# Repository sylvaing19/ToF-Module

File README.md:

# ToF-Module
Time of Flight Module for ranging measurement (hardware + software)

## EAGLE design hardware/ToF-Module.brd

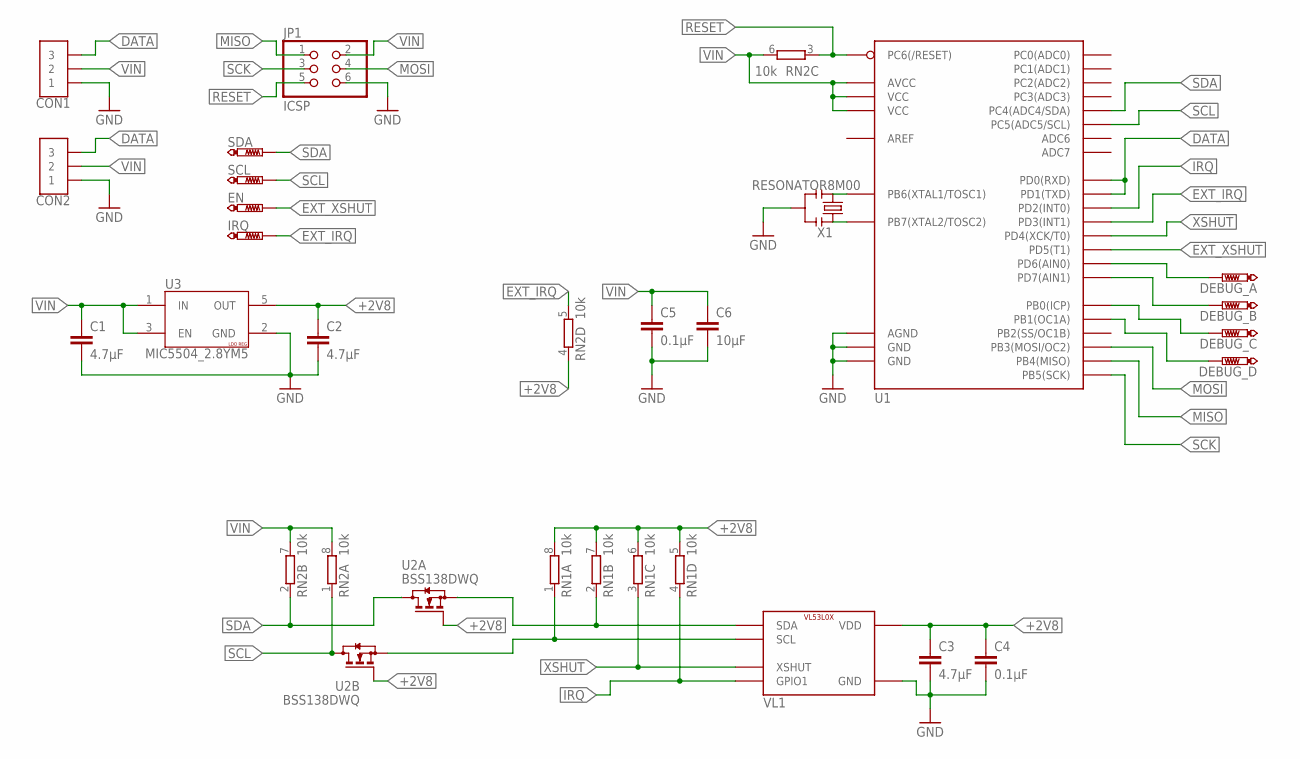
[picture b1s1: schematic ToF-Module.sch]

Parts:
C1, C2, C3: 4.7µF; C0603
C4, C5: 0.1µF; C0603
C6: 10µF; C0805
CON1, CON2: JST-03; GH-03-V
DEBUG_A: PTR1TP15R; TP15R
DEBUG_B: PTR1TP15R; TP15R
DEBUG_C: PTR1TP15R; TP15R
DEBUG_D: PTR1TP15R; TP15R
EN: PTR1TP20SQ; TP20SQ
IRQ: PTR1TP20SQ; TP20SQ
JP1: ICSP; 2X03
RN1, RN2: 10k; CAT16; MOUSER 652-CAT16-103J4LF
SCL: PTR1TP20SQ; TP20SQ
SDA: PTR1TP20SQ; TP20SQ
U1: ATMEGA328P; QFP80P900X900X120-32
U2: BSS138DWQ; SOT65P210X110-6
U3: MIC5504_2.8YM5; SOT95P280X145-5
VL1: VL53L0X
X1: RESONATOR8M00; CSTNE

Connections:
+2V8: C2.1, C3.1, C4.1, RN1.5 (2), RN1.6 (2), RN1.7 (2), RN1.8 (2), RN2.4 (1), U2.G1 (G), U2.G2 (G), U3.5 (OUT), VL1.1 (VDD), VL1.11 (VDD)
DATA: CON1.3, CON2.3, U1.30 (PD0(RXD)), U1.31 (PD1(TXD))
EXT_IRQ: IRQ.TP, RN2.5 (2), U1.1 (PD3(INT1))
EXT_XSHUT: EN.TP, U1.9 (PD5(T1))
GND: C1.2, C2.2, C3.2, C4.2, C5.2, C6.2, CON1.1, CON2.1, JP1.6, U1.3 (GND), U1.5 (AGND), U1.21 (GND), U3.2 (GND), VL1.2 (GND), VL1.3 (GND), VL1.4 (GND), VL1.6 (GND), VL1.12 (GND), X1.2
IRQ: RN1.4 (1), U1.32 (PD2(INT0)), VL1.7 (GPIO1)
MISO: JP1.1, U1.16 (PB4(MISO))
MOSI: JP1.4, U1.15 (PB3(MOSI/OC2))
unnamed: DEBUG_A.TP, U1.10 (PD6(AIN0))
unnamed: DEBUG_B.TP, U1.11 (PD7(AIN1))
unnamed: RN1.2 (1), U2.S1 (S), VL1.9 (SDA)
unnamed: RN1.1, U2.S2 (S), VL1.10 (SCL)
unnamed: U1.7 (PB6(XTAL1/TOSC1)), X1.1
unnamed: U1.8 (PB7(XTAL2/TOSC2)), X1.3
unnamed: DEBUG_C.TP, U1.12 (PB0(ICP))
unnamed: DEBUG_D.TP, U1.13 (PB1(OC1A))
RESET: JP1.5, RN2.3 (1), U1.29 (PC6(/RESET))
SCK: JP1.3, U1.17 (PB5(SCK))
SCL: RN2.1, SCL.TP, U1.28 (PC5(ADC5/SCL)), U2.D2 (D)
SDA: RN2.2 (1), SDA.TP, U1.27 (PC4(ADC4/SDA)), U2.D1 (D)
VIN: C1.1, C5.1, C6.1, CON1.2, CON2.2, JP1.2, RN2.6 (2), RN2.7 (2), RN2.8 (2), U1.4 (VCC), U1.6 (VCC), U1.18 (AVCC), U3.1 (IN), U3.3 (EN)
XSHUT: RN1.3 (1), U1.2 (PD4(XCK/T0)), VL1.5 (XSHUT)

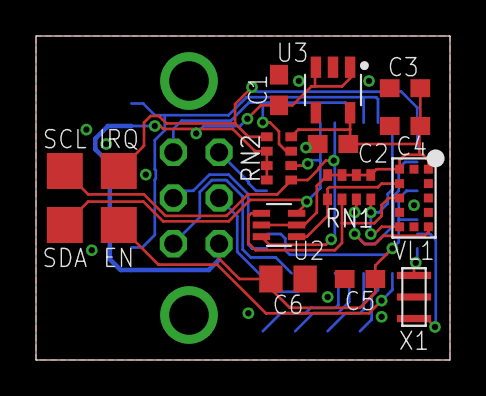
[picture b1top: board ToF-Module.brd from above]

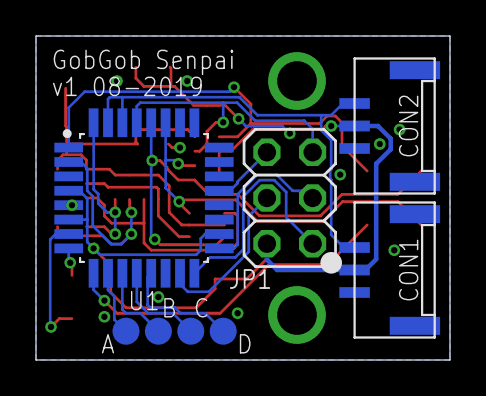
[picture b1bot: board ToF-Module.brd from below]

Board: 2 copper layers, 23.0 x 18.0 mm, 24 parts (8 on the bottom side), 22 nets.

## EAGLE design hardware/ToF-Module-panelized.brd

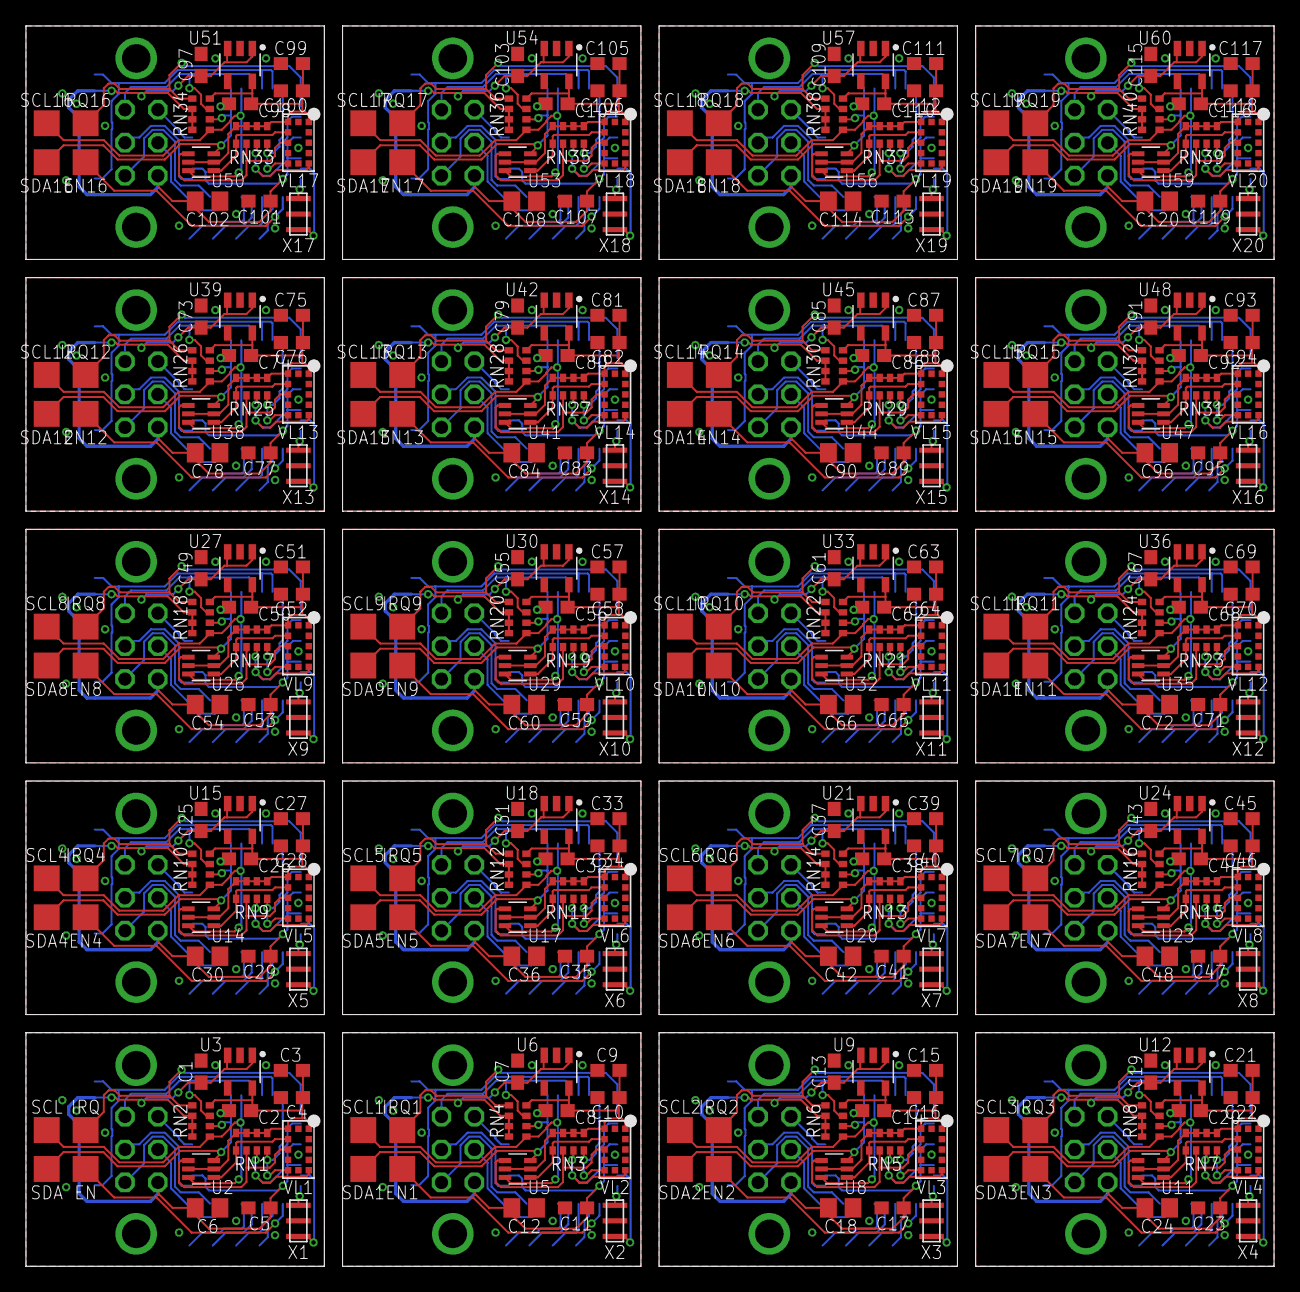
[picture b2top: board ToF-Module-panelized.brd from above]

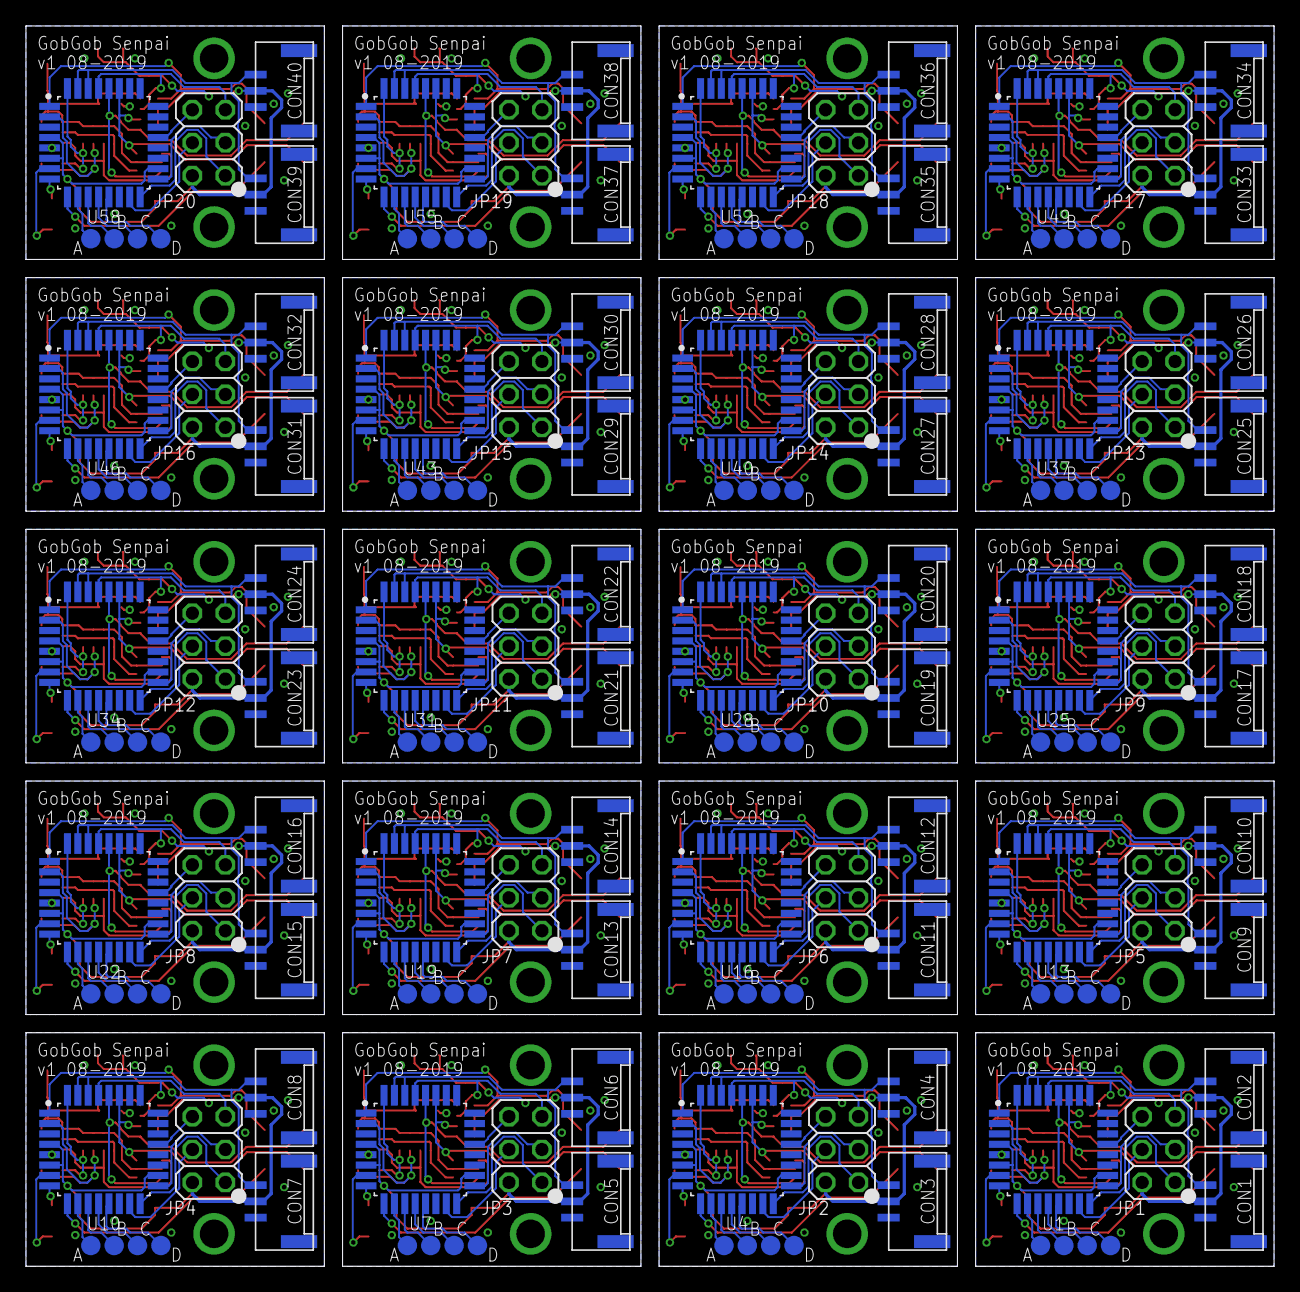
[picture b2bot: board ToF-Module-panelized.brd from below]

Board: 2 copper layers, 96.2 x 95.6 mm, 480 parts (160 on the bottom side), 440 nets.

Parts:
C1, C2, C3, C7, C8, C9, C13, C14, C15, C19, C20, C21, C25, C26, C27, C31, C32, C33, C37, C38, C39, C43, C44, C45, C49, C50, C51, C55, C56, C57, C61, C62, C63, C67, C68, C69, C73, C74, C75, C79, C80, C81, C85, C86, C87, C91, C92, C93, C97, C98, C99, C103, C104, C105, C109, C110, C111, C115, C116, C117: 4.7µF; C0603
C4, C5, C10, C11, C16, C17, C22, C23, C28, C29, C34, C35, C40, C41, C46, C47, C52, C53, C58, C59, C64, C65, C70, C71, C76, C77, C82, C83, C88, C89, C94, C95, C100, C101, C106, C107, C112, C113, C118, C119: 0.1µF; C0603
C6, C12, C18, C24, C30, C36, C42, C48, C54, C60, C66, C72, C78, C84, C90, C96, C102, C108, C114, C120: 10µF; C0805
CON1, CON2, CON3, CON4, CON5, CON6, CON7, CON8, CON9, CON10, CON11, CON12, CON13, CON14, CON15, CON16, CON17, CON18, CON19, CON20, CON21, CON22, CON23, CON24, CON25, CON26, CON27, CON28, CON29, CON30, CON31, CON32, CON33, CON34, CON35, CON36, CON37, CON38, CON39, CON40: JST-03; GH-03-V
DEBUG_A, DEBUG_A1, DEBUG_A2, DEBUG_A3, DEBUG_A4, DEBUG_A5, DEBUG_A6, DEBUG_A7, DEBUG_A8, DEBUG_A9, DEBUG_A10, DEBUG_A11, DEBUG_A12, DEBUG_A13, DEBUG_A14, DEBUG_A15, DEBUG_A16, DEBUG_A17, DEBUG_A18, DEBUG_A19: PTR1TP15R; TP15R
DEBUG_B, DEBUG_B1, DEBUG_B2, DEBUG_B3, DEBUG_B4, DEBUG_B5, DEBUG_B6, DEBUG_B7, DEBUG_B8, DEBUG_B9, DEBUG_B10, DEBUG_B11, DEBUG_B12, DEBUG_B13, DEBUG_B14, DEBUG_B15, DEBUG_B16, DEBUG_B17, DEBUG_B18, DEBUG_B19: PTR1TP15R; TP15R
DEBUG_C, DEBUG_C1, DEBUG_C2, DEBUG_C3, DEBUG_C4, DEBUG_C5, DEBUG_C6, DEBUG_C7, DEBUG_C8, DEBUG_C9, DEBUG_C10, DEBUG_C11, DEBUG_C12, DEBUG_C13, DEBUG_C14, DEBUG_C15, DEBUG_C16, DEBUG_C17, DEBUG_C18, DEBUG_C19: PTR1TP15R; TP15R
DEBUG_D, DEBUG_D1, DEBUG_D2, DEBUG_D3, DEBUG_D4, DEBUG_D5, DEBUG_D6, DEBUG_D7, DEBUG_D8, DEBUG_D9, DEBUG_D10, DEBUG_D11, DEBUG_D12, DEBUG_D13, DEBUG_D14, DEBUG_D15, DEBUG_D16, DEBUG_D17, DEBUG_D18, DEBUG_D19: PTR1TP15R; TP15R
EN, EN1, EN2, EN3, EN4, EN5, EN6, EN7, EN8, EN9, EN10, EN11, EN12, EN13, EN14, EN15, EN16, EN17, EN18, EN19: PTR1TP20SQ; TP20SQ
IRQ, IRQ1, IRQ2, IRQ3, IRQ4, IRQ5, IRQ6, IRQ7, IRQ8, IRQ9, IRQ10, IRQ11, IRQ12, IRQ13, IRQ14, IRQ15, IRQ16, IRQ17, IRQ18, IRQ19: PTR1TP20SQ; TP20SQ
JP1, JP2, JP3, JP4, JP5, JP6, JP7, JP8, JP9, JP10, JP11, JP12, JP13, JP14, JP15, JP16, JP17, JP18, JP19, JP20: ICSP; 2X03
RN1, RN2, RN3, RN4, RN5, RN6, RN7, RN8, RN9, RN10, RN11, RN12, RN13, RN14, RN15, RN16, RN17, RN18, RN19, RN20, RN21, RN22, RN23, RN24, RN25, RN26, RN27, RN28, RN29, RN30, RN31, RN32, RN33, RN34, RN35, RN36, RN37, RN38, RN39, RN40: 10k; CAT16
SCL, SCL1, SCL2, SCL3, SCL4, SCL5, SCL6, SCL7, SCL8, SCL9, SCL10, SCL11, SCL12, SCL13, SCL14, SCL15, SCL16, SCL17, SCL18, SCL19: PTR1TP20SQ; TP20SQ
SDA, SDA1, SDA2, SDA3, SDA4, SDA5, SDA6, SDA7, SDA8, SDA9, SDA10, SDA11, SDA12, SDA13, SDA14, SDA15, SDA16, SDA17, SDA18, SDA19: PTR1TP20SQ; TP20SQ
U1, U4, U7, U10, U13, U16, U19, U22, U25, U28, U31, U34, U37, U40, U43, U46, U49, U52, U55, U58: ATMEGA328P; QFP80P900X900X120-32
U2, U5, U8, U11, U14, U17, U20, U23, U26, U29, U32, U35, U38, U41, U44, U47, U50, U53, U56, U59: BSS138DWQ; SOT65P210X110-6
U3, U6, U9, U12, U15, U18, U21, U24, U27, U30, U33, U36, U39, U42, U45, U48, U51, U54, U57, U60: MIC5504_2.8YM5; SOT95P280X145-5
VL1, VL2, VL3, VL4, VL5, VL6, VL7, VL8, VL9, VL10, VL11, VL12, VL13, VL14, VL15, VL16, VL17, VL18, VL19, VL20: VL53L0X
X1, X2, X3, X4, X5, X6, X7, X8, X9, X10, X11, X12, X13, X14, X15, X16, X17, X18, X19, X20: RESONATOR8M00; CSTNE

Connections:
+2V1: C8.1, C9.1, C10.1, RN3.5, RN3.6, RN3.7, RN3.8, RN4.4, U5.G1, U5.G2, U6.5, VL2.1, VL2.11
+2V2: C14.1, C15.1, C16.1, RN5.5, RN5.6, RN5.7, RN5.8, RN6.4, U8.G1, U8.G2, U9.5, VL3.1, VL3.11
+2V3: C20.1, C21.1, C22.1, RN7.5, RN7.6, RN7.7, RN7.8, RN8.4, U11.G1, U11.G2, U12.5, VL4.1, VL4.11
+2V4: C26.1, C27.1, C28.1, RN9.5, RN9.6, RN9.7, RN9.8, RN10.4, U14.G1, U14.G2, U15.5, VL5.1, VL5.11
+2V5: C32.1, C33.1, C34.1, RN11.5, RN11.6, RN11.7, RN11.8, RN12.4, U17.G1, U17.G2, U18.5, VL6.1, VL6.11
+2V6: C38.1, C39.1, C40.1, RN13.5, RN13.6, RN13.7, RN13.8, RN14.4, U20.G1, U20.G2, U21.5, VL7.1, VL7.11
+2V7: C44.1, C45.1, C46.1, RN15.5, RN15.6, RN15.7, RN15.8, RN16.4, U23.G1, U23.G2, U24.5, VL8.1, VL8.11
+2V8: C2.1, C3.1, C4.1, RN1.5, RN1.6, RN1.7, RN1.8, RN2.4, U2.G1, U2.G2, U3.5, VL1.1, VL1.11
+2V9: C50.1, C51.1, C52.1, RN17.5, RN17.6, RN17.7, RN17.8, RN18.4, U26.G1, U26.G2, U27.5, VL9.1, VL9.11
+2V10: C56.1, C57.1, C58.1, RN19.5, RN19.6, RN19.7, RN19.8, RN20.4, U29.G1, U29.G2, U30.5, VL10.1, VL10.11
+2V11: C62.1, C63.1, C64.1, RN21.5, RN21.6, RN21.7, RN21.8, RN22.4, U32.G1, U32.G2, U33.5, VL11.1, VL11.11
+2V12: C68.1, C69.1, C70.1, RN23.5, RN23.6, RN23.7, RN23.8, RN24.4, U35.G1, U35.G2, U36.5, VL12.1, VL12.11
+2V13: C74.1, C75.1, C76.1, RN25.5, RN25.6, RN25.7, RN25.8, RN26.4, U38.G1, U38.G2, U39.5, VL13.1, VL13.11
+2V14: C80.1, C81.1, C82.1, RN27.5, RN27.6, RN27.7, RN27.8, RN28.4, U41.G1, U41.G2, U42.5, VL14.1, VL14.11
+2V15: C86.1, C87.1, C88.1, RN29.5, RN29.6, RN29.7, RN29.8, RN30.4, U44.G1, U44.G2, U45.5, VL15.1, VL15.11
+2V16: C92.1, C93.1, C94.1, RN31.5, RN31.6, RN31.7, RN31.8, RN32.4, U47.G1, U47.G2, U48.5, VL16.1, VL16.11
+2V17: C98.1, C99.1, C100.1, RN33.5, RN33.6, RN33.7, RN33.8, RN34.4, U50.G1, U50.G2, U51.5, VL17.1, VL17.11
+2V18: C104.1, C105.1, C106.1, RN35.5, RN35.6, RN35.7, RN35.8, RN36.4, U53.G1, U53.G2, U54.5, VL18.1, VL18.11
+2V19: C110.1, C111.1, C112.1, RN37.5, RN37.6, RN37.7, RN37.8, RN38.4, U56.G1, U56.G2, U57.5, VL19.1, VL19.11
+2V20: C116.1, C117.1, C118.1, RN39.5, RN39.6, RN39.7, RN39.8, RN40.4, U59.G1, U59.G2, U60.5, VL20.1, VL20.11
DATA: CON1.3, CON2.3, U1.30, U1.31
DATA1: CON3.3, CON4.3, U4.30, U4.31
DATA2: CON5.3, CON6.3, U7.30, U7.31
DATA3: CON7.3, CON8.3, U10.30, U10.31
DATA4: CON9.3, CON10.3, U13.30, U13.31
DATA5: CON11.3, CON12.3, U16.30, U16.31
DATA6: CON13.3, CON14.3, U19.30, U19.31
DATA7: CON15.3, CON16.3, U22.30, U22.31
DATA8: CON17.3, CON18.3, U25.30, U25.31
DATA9: CON19.3, CON20.3, U28.30, U28.31
DATA10: CON21.3, CON22.3, U31.30, U31.31
DATA11: CON23.3, CON24.3, U34.30, U34.31
DATA12: CON25.3, CON26.3, U37.30, U37.31
DATA13: CON27.3, CON28.3, U40.30, U40.31
DATA14: CON29.3, CON30.3, U43.30, U43.31
DATA15: CON31.3, CON32.3, U46.30, U46.31
DATA16: CON33.3, CON34.3, U49.30, U49.31
DATA17: CON35.3, CON36.3, U52.30, U52.31
DATA18: CON37.3, CON38.3, U55.30, U55.31
DATA19: CON39.3, CON40.3, U58.30, U58.31
EXT_IRQ: IRQ.TP, RN2.5, U1.1
EXT_IRQ1: IRQ1.TP, RN4.5, U4.1
EXT_IRQ2: IRQ2.TP, RN6.5, U7.1
EXT_IRQ3: IRQ3.TP, RN8.5, U10.1
EXT_IRQ4: IRQ4.TP, RN10.5, U13.1
EXT_IRQ5: IRQ5.TP, RN12.5, U16.1
EXT_IRQ6: IRQ6.TP, RN14.5, U19.1
EXT_IRQ7: IRQ7.TP, RN16.5, U22.1
EXT_IRQ8: IRQ8.TP, RN18.5, U25.1
EXT_IRQ9: IRQ9.TP, RN20.5, U28.1
EXT_IRQ10: IRQ10.TP, RN22.5, U31.1
EXT_IRQ11: IRQ11.TP, RN24.5, U34.1
EXT_IRQ12: IRQ12.TP, RN26.5, U37.1
EXT_IRQ13: IRQ13.TP, RN28.5, U40.1
EXT_IRQ14: IRQ14.TP, RN30.5, U43.1
EXT_IRQ15: IRQ15.TP, RN32.5, U46.1
EXT_IRQ16: IRQ16.TP, RN34.5, U49.1
EXT_IRQ17: IRQ17.TP, RN36.5, U52.1
EXT_IRQ18: IRQ18.TP, RN38.5, U55.1
EXT_IRQ19: IRQ19.TP, RN40.5, U58.1
EXT_XSHUT: EN.TP, U1.9
EXT_XSHUT1: EN1.TP, U4.9
EXT_XSHUT2: EN2.TP, U7.9
EXT_XSHUT3: EN3.TP, U10.9
EXT_XSHUT4: EN4.TP, U13.9
EXT_XSHUT5: EN5.TP, U16.9
EXT_XSHUT6: EN6.TP, U19.9
EXT_XSHUT7: EN7.TP, U22.9
EXT_XSHUT8: EN8.TP, U25.9
EXT_XSHUT9: EN9.TP, U28.9
EXT_XSHUT10: EN10.TP, U31.9
EXT_XSHUT11: EN11.TP, U34.9
EXT_XSHUT12: EN12.TP, U37.9
EXT_XSHUT13: EN13.TP, U40.9
EXT_XSHUT14: EN14.TP, U43.9
EXT_XSHUT15: EN15.TP, U46.9
EXT_XSHUT16: EN16.TP, U49.9
EXT_XSHUT17: EN17.TP, U52.9
EXT_XSHUT18: EN18.TP, U55.9
EXT_XSHUT19: EN19.TP, U58.9
GND: C1.2, C2.2, C3.2, C4.2, C5.2, C6.2, CON1.1, CON2.1, JP1.6, U1.3, U1.5, U1.21, U3.2, VL1.2, VL1.3, VL1.4, VL1.6, VL1.12, X1.2
GND1: C7.2, C8.2, C9.2, C10.2, C11.2, C12.2, CON3.1, CON4.1, JP2.6, U4.3, U4.5, U4.21, U6.2, VL2.2, VL2.3, VL2.4, VL2.6, VL2.12, X2.2
GND2: C13.2, C14.2, C15.2, C16.2, C17.2, C18.2, CON5.1, CON6.1, JP3.6, U7.3, U7.5, U7.21, U9.2, VL3.2, VL3.3, VL3.4, VL3.6, VL3.12, X3.2
GND3: C19.2, C20.2, C21.2, C22.2, C23.2, C24.2, CON7.1, CON8.1, JP4.6, U10.3, U10.5, U10.21, U12.2, VL4.2, VL4.3, VL4.4, VL4.6, VL4.12, X4.2
GND4: C25.2, C26.2, C27.2, C28.2, C29.2, C30.2, CON9.1, CON10.1, JP5.6, U13.3, U13.5, U13.21, U15.2, VL5.2, VL5.3, VL5.4, VL5.6, VL5.12, X5.2
GND5: C31.2, C32.2, C33.2, C34.2, C35.2, C36.2, CON11.1, CON12.1, JP6.6, U16.3, U16.5, U16.21, U18.2, VL6.2, VL6.3, VL6.4, VL6.6, VL6.12, X6.2
GND6: C37.2, C38.2, C39.2, C40.2, C41.2, C42.2, CON13.1, CON14.1, JP7.6, U19.3, U19.5, U19.21, U21.2, VL7.2, VL7.3, VL7.4, VL7.6, VL7.12, X7.2
GND7: C43.2, C44.2, C45.2, C46.2, C47.2, C48.2, CON15.1, CON16.1, JP8.6, U22.3, U22.5, U22.21, U24.2, VL8.2, VL8.3, VL8.4, VL8.6, VL8.12, X8.2
GND8: C49.2, C50.2, C51.2, C52.2, C53.2, C54.2, CON17.1, CON18.1, JP9.6, U25.3, U25.5, U25.21, U27.2, VL9.2, VL9.3, VL9.4, VL9.6, VL9.12, X9.2
GND9: C55.2, C56.2, C57.2, C58.2, C59.2, C60.2, CON19.1, CON20.1, JP10.6, U28.3, U28.5, U28.21, U30.2, VL10.2, VL10.3, VL10.4, VL10.6, VL10.12, X10.2
GND10: C61.2, C62.2, C63.2, C64.2, C65.2, C66.2, CON21.1, CON22.1, JP11.6, U31.3, U31.5, U31.21, U33.2, VL11.2, VL11.3, VL11.4, VL11.6, VL11.12, X11.2
GND11: C67.2, C68.2, C69.2, C70.2, C71.2, C72.2, CON23.1, CON24.1, JP12.6, U34.3, U34.5, U34.21, U36.2, VL12.2, VL12.3, VL12.4, VL12.6, VL12.12, X12.2
GND12: C73.2, C74.2, C75.2, C76.2, C77.2, C78.2, CON25.1, CON26.1, JP13.6, U37.3, U37.5, U37.21, U39.2, VL13.2, VL13.3, VL13.4, VL13.6, VL13.12, X13.2
GND13: C79.2, C80.2, C81.2, C82.2, C83.2, C84.2, CON27.1, CON28.1, JP14.6, U40.3, U40.5, U40.21, U42.2, VL14.2, VL14.3, VL14.4, VL14.6, VL14.12, X14.2
GND14: C85.2, C86.2, C87.2, C88.2, C89.2, C90.2, CON29.1, CON30.1, JP15.6, U43.3, U43.5, U43.21, U45.2, VL15.2, VL15.3, VL15.4, VL15.6, VL15.12, X15.2
GND15: C91.2, C92.2, C93.2, C94.2, C95.2, C96.2, CON31.1, CON32.1, JP16.6, U46.3, U46.5, U46.21, U48.2, VL16.2, VL16.3, VL16.4, VL16.6, VL16.12, X16.2
GND16: C97.2, C98.2, C99.2, C100.2, C101.2, C102.2, CON33.1, CON34.1, JP17.6, U49.3, U49.5, U49.21, U51.2, VL17.2, VL17.3, VL17.4, VL17.6, VL17.12, X17.2
GND17: C103.2, C104.2, C105.2, C106.2, C107.2, C108.2, CON35.1, CON36.1, JP18.6, U52.3, U52.5, U52.21, U54.2, VL18.2, VL18.3, VL18.4, VL18.6, VL18.12, X18.2
GND18: C109.2, C110.2, C111.2, C112.2, C113.2, C114.2, CON37.1, CON38.1, JP19.6, U55.3, U55.5, U55.21, U57.2, VL19.2, VL19.3, VL19.4, VL19.6, VL19.12, X19.2
GND19: C115.2, C116.2, C117.2, C118.2, C119.2, C120.2, CON39.1, CON40.1, JP20.6, U58.3, U58.5, U58.21, U60.2, VL20.2, VL20.3, VL20.4, VL20.6, VL20.12, X20.2
IRQ: RN1.4, U1.32, VL1.7
IRQ1: RN3.4, U4.32, VL2.7
IRQ2: RN5.4, U7.32, VL3.7
IRQ3: RN7.4, U10.32, VL4.7
IRQ4: RN9.4, U13.32, VL5.7
IRQ5: RN11.4, U16.32, VL6.7
IRQ6: RN13.4, U19.32, VL7.7
IRQ7: RN15.4, U22.32, VL8.7
IRQ8: RN17.4, U25.32, VL9.7
IRQ9: RN19.4, U28.32, VL10.7
IRQ10: RN21.4, U31.32, VL11.7
IRQ11: RN23.4, U34.32, VL12.7
IRQ12: RN25.4, U37.32, VL13.7
IRQ13: RN27.4, U40.32, VL14.7
IRQ14: RN29.4, U43.32, VL15.7
IRQ15: RN31.4, U46.32, VL16.7
IRQ16: RN33.4, U49.32, VL17.7
IRQ17: RN35.4, U52.32, VL18.7
IRQ18: RN37.4, U55.32, VL19.7
IRQ19: RN39.4, U58.32, VL20.7
MISO: JP1.1, U1.16
MISO1: JP2.1, U4.16
MISO2: JP3.1, U7.16
MISO3: JP4.1, U10.16
MISO4: JP5.1, U13.16
MISO5: JP6.1, U16.16
MISO6: JP7.1, U19.16
MISO7: JP8.1, U22.16
MISO8: JP9.1, U25.16
MISO9: JP10.1, U28.16
MISO10: JP11.1, U31.16
MISO11: JP12.1, U34.16
MISO12: JP13.1, U37.16
MISO13: JP14.1, U40.16
MISO14: JP15.1, U43.16
MISO15: JP16.1, U46.16
MISO16: JP17.1, U49.16
MISO17: JP18.1, U52.16
MISO18: JP19.1, U55.16
MISO19: JP20.1, U58.16
MOSI: JP1.4, U1.15
MOSI1: JP2.4, U4.15
MOSI2: JP3.4, U7.15
MOSI3: JP4.4, U10.15
MOSI4: JP5.4, U13.15
MOSI5: JP6.4, U16.15
MOSI6: JP7.4, U19.15
MOSI7: JP8.4, U22.15
MOSI8: JP9.4, U25.15
MOSI9: JP10.4, U28.15
MOSI10: JP11.4, U31.15
MOSI11: JP12.4, U34.15
MOSI12: JP13.4, U37.15
MOSI13: JP14.4, U40.15
MOSI14: JP15.4, U43.15
MOSI15: JP16.4, U46.15
MOSI16: JP17.4, U49.15
MOSI17: JP18.4, U52.15
MOSI18: JP19.4, U55.15
MOSI19: JP20.4, U58.15
unnamed: DEBUG_A.TP, U1.10
unnamed: DEBUG_B.TP, U1.11
unnamed: RN1.2, U2.S1, VL1.9
unnamed: RN1.1, U2.S2, VL1.10
unnamed: U1.7, X1.1
unnamed: U1.8, X1.3
unnamed: DEBUG_C.TP, U1.12
unnamed: DEBUG_D.TP, U1.13
unnamed: RN3.2, U5.S1, VL2.9
unnamed: RN3.1, U5.S2, VL2.10
unnamed: U4.7, X2.1
unnamed: U4.8, X2.3
unnamed: DEBUG_A1.TP, U4.10
unnamed: DEBUG_B1.TP, U4.11
unnamed: DEBUG_C1.TP, U4.12
unnamed: DEBUG_D1.TP, U4.13
unnamed: RN5.2, U8.S1, VL3.9
unnamed: RN5.1, U8.S2, VL3.10
unnamed: U7.7, X3.1
unnamed: U7.8, X3.3
unnamed: DEBUG_A2.TP, U7.10
unnamed: DEBUG_B2.TP, U7.11
unnamed: DEBUG_C2.TP, U7.12
unnamed: DEBUG_D2.TP, U7.13
unnamed: RN7.2, U11.S1, VL4.9
unnamed: RN7.1, U11.S2, VL4.10
unnamed: U10.7, X4.1
unnamed: U10.8, X4.3
unnamed: DEBUG_A3.TP, U10.10
unnamed: DEBUG_B3.TP, U10.11
unnamed: DEBUG_C3.TP, U10.12
unnamed: DEBUG_D3.TP, U10.13
unnamed: RN9.2, U14.S1, VL5.9
unnamed: RN9.1, U14.S2, VL5.10
unnamed: U13.7, X5.1
unnamed: U13.8, X5.3
unnamed: DEBUG_A4.TP, U13.10
unnamed: DEBUG_B4.TP, U13.11
unnamed: DEBUG_C4.TP, U13.12
unnamed: DEBUG_D4.TP, U13.13
unnamed: RN11.2, U17.S1, VL6.9
unnamed: RN11.1, U17.S2, VL6.10
unnamed: U16.7, X6.1
unnamed: U16.8, X6.3
unnamed: DEBUG_A5.TP, U16.10
unnamed: DEBUG_B5.TP, U16.11
unnamed: DEBUG_C5.TP, U16.12
unnamed: DEBUG_D5.TP, U16.13
unnamed: RN13.2, U20.S1, VL7.9
unnamed: RN13.1, U20.S2, VL7.10
unnamed: U19.7, X7.1
unnamed: U19.8, X7.3
unnamed: DEBUG_A6.TP, U19.10
unnamed: DEBUG_B6.TP, U19.11
unnamed: DEBUG_C6.TP, U19.12
unnamed: DEBUG_D6.TP, U19.13
unnamed: RN15.2, U23.S1, VL8.9
unnamed: RN15.1, U23.S2, VL8.10
unnamed: U22.7, X8.1
unnamed: U22.8, X8.3
unnamed: DEBUG_A7.TP, U22.10
unnamed: DEBUG_B7.TP, U22.11
unnamed: DEBUG_C7.TP, U22.12
unnamed: DEBUG_D7.TP, U22.13
unnamed: RN17.2, U26.S1, VL9.9
unnamed: RN17.1, U26.S2, VL9.10
unnamed: U25.7, X9.1
unnamed: U25.8, X9.3
unnamed: DEBUG_A8.TP, U25.10
unnamed: DEBUG_B8.TP, U25.11
unnamed: DEBUG_C8.TP, U25.12
unnamed: DEBUG_D8.TP, U25.13
unnamed: RN19.2, U29.S1, VL10.9
unnamed: RN19.1, U29.S2, VL10.10
unnamed: U28.7, X10.1
unnamed: U28.8, X10.3
unnamed: DEBUG_A9.TP, U28.10
unnamed: DEBUG_B9.TP, U28.11
unnamed: DEBUG_C9.TP, U28.12
unnamed: DEBUG_D9.TP, U28.13
unnamed: RN21.2, U32.S1, VL11.9
unnamed: RN21.1, U32.S2, VL11.10
unnamed: U31.7, X11.1
unnamed: U31.8, X11.3
unnamed: DEBUG_A10.TP, U31.10
unnamed: DEBUG_B10.TP, U31.11
unnamed: DEBUG_C10.TP, U31.12
unnamed: DEBUG_D10.TP, U31.13
unnamed: RN23.2, U35.S1, VL12.9
unnamed: RN23.1, U35.S2, VL12.10
unnamed: U34.7, X12.1
unnamed: U34.8, X12.3
unnamed: DEBUG_A11.TP, U34.10
unnamed: DEBUG_B11.TP, U34.11
unnamed: DEBUG_C11.TP, U34.12
unnamed: DEBUG_D11.TP, U34.13
unnamed: RN25.2, U38.S1, VL13.9
unnamed: RN25.1, U38.S2, VL13.10
unnamed: U37.7, X13.1
unnamed: U37.8, X13.3
unnamed: DEBUG_A12.TP, U37.10
unnamed: DEBUG_B12.TP, U37.11
unnamed: DEBUG_C12.TP, U37.12
unnamed: DEBUG_D12.TP, U37.13
unnamed: RN27.2, U41.S1, VL14.9
unnamed: RN27.1, U41.S2, VL14.10
unnamed: U40.7, X14.1
unnamed: U40.8, X14.3
unnamed: DEBUG_A13.TP, U40.10
unnamed: DEBUG_B13.TP, U40.11
unnamed: DEBUG_C13.TP, U40.12
unnamed: DEBUG_D13.TP, U40.13
unnamed: RN29.2, U44.S1, VL15.9
unnamed: RN29.1, U44.S2, VL15.10
unnamed: U43.7, X15.1
unnamed: U43.8, X15.3
unnamed: DEBUG_A14.TP, U43.10
unnamed: DEBUG_B14.TP, U43.11
unnamed: DEBUG_C14.TP, U43.12
unnamed: DEBUG_D14.TP, U43.13
unnamed: RN31.2, U47.S1, VL16.9
unnamed: RN31.1, U47.S2, VL16.10
unnamed: U46.7, X16.1
unnamed: U46.8, X16.3
unnamed: DEBUG_A15.TP, U46.10
unnamed: DEBUG_B15.TP, U46.11
unnamed: DEBUG_C15.TP, U46.12
unnamed: DEBUG_D15.TP, U46.13
unnamed: RN33.2, U50.S1, VL17.9
unnamed: RN33.1, U50.S2, VL17.10
unnamed: U49.7, X17.1
unnamed: U49.8, X17.3
unnamed: DEBUG_A16.TP, U49.10
unnamed: DEBUG_B16.TP, U49.11
unnamed: DEBUG_C16.TP, U49.12
unnamed: DEBUG_D16.TP, U49.13
unnamed: RN35.2, U53.S1, VL18.9
unnamed: RN35.1, U53.S2, VL18.10
unnamed: U52.7, X18.1
unnamed: U52.8, X18.3
unnamed: DEBUG_A17.TP, U52.10
unnamed: DEBUG_B17.TP, U52.11
unnamed: DEBUG_C17.TP, U52.12
unnamed: DEBUG_D17.TP, U52.13
unnamed: RN37.2, U56.S1, VL19.9
unnamed: RN37.1, U56.S2, VL19.10
unnamed: U55.7, X19.1
unnamed: U55.8, X19.3
unnamed: DEBUG_A18.TP, U55.10
unnamed: DEBUG_B18.TP, U55.11
unnamed: DEBUG_C18.TP, U55.12
unnamed: DEBUG_D18.TP, U55.13
unnamed: RN39.2, U59.S1, VL20.9
unnamed: RN39.1, U59.S2, VL20.10
unnamed: U58.7, X20.1
unnamed: U58.8, X20.3
unnamed: DEBUG_A19.TP, U58.10
unnamed: DEBUG_B19.TP, U58.11
unnamed: DEBUG_C19.TP, U58.12
unnamed: DEBUG_D19.TP, U58.13
RESET: JP1.5, RN2.3, U1.29
RESET1: JP2.5, RN4.3, U4.29
RESET2: JP3.5, RN6.3, U7.29
RESET3: JP4.5, RN8.3, U10.29
RESET4: JP5.5, RN10.3, U13.29
RESET5: JP6.5, RN12.3, U16.29
RESET6: JP7.5, RN14.3, U19.29
RESET7: JP8.5, RN16.3, U22.29
RESET8: JP9.5, RN18.3, U25.29
RESET9: JP10.5, RN20.3, U28.29
RESET10: JP11.5, RN22.3, U31.29
RESET11: JP12.5, RN24.3, U34.29
RESET12: JP13.5, RN26.3, U37.29
RESET13: JP14.5, RN28.3, U40.29
RESET14: JP15.5, RN30.3, U43.29
RESET15: JP16.5, RN32.3, U46.29
RESET16: JP17.5, RN34.3, U49.29
RESET17: JP18.5, RN36.3, U52.29
RESET18: JP19.5, RN38.3, U55.29
RESET19: JP20.5, RN40.3, U58.29
SCK: JP1.3, U1.17
SCK1: JP2.3, U4.17
SCK2: JP3.3, U7.17
SCK3: JP4.3, U10.17
SCK4: JP5.3, U13.17
SCK5: JP6.3, U16.17
SCK6: JP7.3, U19.17
SCK7: JP8.3, U22.17
SCK8: JP9.3, U25.17
SCK9: JP10.3, U28.17
SCK10: JP11.3, U31.17
SCK11: JP12.3, U34.17
SCK12: JP13.3, U37.17
SCK13: JP14.3, U40.17
SCK14: JP15.3, U43.17
SCK15: JP16.3, U46.17
SCK16: JP17.3, U49.17
SCK17: JP18.3, U52.17
SCK18: JP19.3, U55.17
SCK19: JP20.3, U58.17
SCL: RN2.1, SCL.TP, U1.28, U2.D2
SCL1: RN4.1, SCL1.TP, U4.28, U5.D2
SCL2: RN6.1, SCL2.TP, U7.28, U8.D2
SCL3: RN8.1, SCL3.TP, U10.28, U11.D2
SCL4: RN10.1, SCL4.TP, U13.28, U14.D2
SCL5: RN12.1, SCL5.TP, U16.28, U17.D2
SCL6: RN14.1, SCL6.TP, U19.28, U20.D2
SCL7: RN16.1, SCL7.TP, U22.28, U23.D2
SCL8: RN18.1, SCL8.TP, U25.28, U26.D2
SCL9: RN20.1, SCL9.TP, U28.28, U29.D2
SCL10: RN22.1, SCL10.TP, U31.28, U32.D2
SCL11: RN24.1, SCL11.TP, U34.28, U35.D2
SCL12: RN26.1, SCL12.TP, U37.28, U38.D2
SCL13: RN28.1, SCL13.TP, U40.28, U41.D2
SCL14: RN30.1, SCL14.TP, U43.28, U44.D2
SCL15: RN32.1, SCL15.TP, U46.28, U47.D2
SCL16: RN34.1, SCL16.TP, U49.28, U50.D2
SCL17: RN36.1, SCL17.TP, U52.28, U53.D2
SCL18: RN38.1, SCL18.TP, U55.28, U56.D2
SCL19: RN40.1, SCL19.TP, U58.28, U59.D2
SDA: RN2.2, SDA.TP, U1.27, U2.D1
SDA1: RN4.2, SDA1.TP, U4.27, U5.D1
SDA2: RN6.2, SDA2.TP, U7.27, U8.D1
SDA3: RN8.2, SDA3.TP, U10.27, U11.D1
SDA4: RN10.2, SDA4.TP, U13.27, U14.D1
SDA5: RN12.2, SDA5.TP, U16.27, U17.D1
SDA6: RN14.2, SDA6.TP, U19.27, U20.D1
SDA7: RN16.2, SDA7.TP, U22.27, U23.D1
SDA8: RN18.2, SDA8.TP, U25.27, U26.D1
SDA9: RN20.2, SDA9.TP, U28.27, U29.D1
SDA10: RN22.2, SDA10.TP, U31.27, U32.D1
SDA11: RN24.2, SDA11.TP, U34.27, U35.D1
SDA12: RN26.2, SDA12.TP, U37.27, U38.D1
SDA13: RN28.2, SDA13.TP, U40.27, U41.D1
SDA14: RN30.2, SDA14.TP, U43.27, U44.D1
SDA15: RN32.2, SDA15.TP, U46.27, U47.D1
SDA16: RN34.2, SDA16.TP, U49.27, U50.D1
SDA17: RN36.2, SDA17.TP, U52.27, U53.D1
SDA18: RN38.2, SDA18.TP, U55.27, U56.D1
SDA19: RN40.2, SDA19.TP, U58.27, U59.D1
VIN: C1.1, C5.1, C6.1, CON1.2, CON2.2, JP1.2, RN2.6, RN2.7, RN2.8, U1.4, U1.6, U1.18, U3.1, U3.3
VIN1: C7.1, C11.1, C12.1, CON3.2, CON4.2, JP2.2, RN4.6, RN4.7, RN4.8, U4.4, U4.6, U4.18, U6.1, U6.3
VIN2: C13.1, C17.1, C18.1, CON5.2, CON6.2, JP3.2, RN6.6, RN6.7, RN6.8, U7.4, U7.6, U7.18, U9.1, U9.3
VIN3: C19.1, C23.1, C24.1, CON7.2, CON8.2, JP4.2, RN8.6, RN8.7, RN8.8, U10.4, U10.6, U10.18, U12.1, U12.3
VIN4: C25.1, C29.1, C30.1, CON9.2, CON10.2, JP5.2, RN10.6, RN10.7, RN10.8, U13.4, U13.6, U13.18, U15.1, U15.3
VIN5: C31.1, C35.1, C36.1, CON11.2, CON12.2, JP6.2, RN12.6, RN12.7, RN12.8, U16.4, U16.6, U16.18, U18.1, U18.3
VIN6: C37.1, C41.1, C42.1, CON13.2, CON14.2, JP7.2, RN14.6, RN14.7, RN14.8, U19.4, U19.6, U19.18, U21.1, U21.3
VIN7: C43.1, C47.1, C48.1, CON15.2, CON16.2, JP8.2, RN16.6, RN16.7, RN16.8, U22.4, U22.6, U22.18, U24.1, U24.3
VIN8: C49.1, C53.1, C54.1, CON17.2, CON18.2, JP9.2, RN18.6, RN18.7, RN18.8, U25.4, U25.6, U25.18, U27.1, U27.3
VIN9: C55.1, C59.1, C60.1, CON19.2, CON20.2, JP10.2, RN20.6, RN20.7, RN20.8, U28.4, U28.6, U28.18, U30.1, U30.3
VIN10: C61.1, C65.1, C66.1, CON21.2, CON22.2, JP11.2, RN22.6, RN22.7, RN22.8, U31.4, U31.6, U31.18, U33.1, U33.3
VIN11: C67.1, C71.1, C72.1, CON23.2, CON24.2, JP12.2, RN24.6, RN24.7, RN24.8, U34.4, U34.6, U34.18, U36.1, U36.3
VIN12: C73.1, C77.1, C78.1, CON25.2, CON26.2, JP13.2, RN26.6, RN26.7, RN26.8, U37.4, U37.6, U37.18, U39.1, U39.3
VIN13: C79.1, C83.1, C84.1, CON27.2, CON28.2, JP14.2, RN28.6, RN28.7, RN28.8, U40.4, U40.6, U40.18, U42.1, U42.3
VIN14: C85.1, C89.1, C90.1, CON29.2, CON30.2, JP15.2, RN30.6, RN30.7, RN30.8, U43.4, U43.6, U43.18, U45.1, U45.3
VIN15: C91.1, C95.1, C96.1, CON31.2, CON32.2, JP16.2, RN32.6, RN32.7, RN32.8, U46.4, U46.6, U46.18, U48.1, U48.3
VIN16: C97.1, C101.1, C102.1, CON33.2, CON34.2, JP17.2, RN34.6, RN34.7, RN34.8, U49.4, U49.6, U49.18, U51.1, U51.3
VIN17: C103.1, C107.1, C108.1, CON35.2, CON36.2, JP18.2, RN36.6, RN36.7, RN36.8, U52.4, U52.6, U52.18, U54.1, U54.3
VIN18: C109.1, C113.1, C114.1, CON37.2, CON38.2, JP19.2, RN38.6, RN38.7, RN38.8, U55.4, U55.6, U55.18, U57.1, U57.3
VIN19: C115.1, C119.1, C120.1, CON39.2, CON40.2, JP20.2, RN40.6, RN40.7, RN40.8, U58.4, U58.6, U58.18, U60.1, U60.3
XSHUT: RN1.3, U1.2, VL1.5
XSHUT1: RN3.3, U4.2, VL2.5
XSHUT2: RN5.3, U7.2, VL3.5
XSHUT3: RN7.3, U10.2, VL4.5
XSHUT4: RN9.3, U13.2, VL5.5
XSHUT5: RN11.3, U16.2, VL6.5
XSHUT6: RN13.3, U19.2, VL7.5
XSHUT7: RN15.3, U22.2, VL8.5
XSHUT8: RN17.3, U25.2, VL9.5
XSHUT9: RN19.3, U28.2, VL10.5
XSHUT10: RN21.3, U31.2, VL11.5
XSHUT11: RN23.3, U34.2, VL12.5
XSHUT12: RN25.3, U37.2, VL13.5
XSHUT13: RN27.3, U40.2, VL14.5
XSHUT14: RN29.3, U43.2, VL15.5
XSHUT15: RN31.3, U46.2, VL16.5
XSHUT16: RN33.3, U49.2, VL17.5
XSHUT17: RN35.3, U52.2, VL18.5
XSHUT18: RN37.3, U55.2, VL19.5
XSHUT19: RN39.3, U58.2, VL20.5

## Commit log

2019-08-12 add eagle lib for VL sensors
2019-08-14 hardware: WIP, schematics mostly done
2019-08-15 PCB: first version
2019-08-15 Add Gerber files + BOM
2019-08-15 Add PDF schematics
2019-08-17 Reorganize files
2019-09-02 software: started architecture design
2019-09-03 firmware: register_storage implemented
2019-09-04 start to implement sensor_mgr
2019-09-07 firmware: sensor_mgr implemented
2019-09-14 firmware: various bugfixes
2019-09-20 add arduino lib to control Modules
2019-09-20 remove debug hacks from the firmware
2019-09-20 hardware: add pullup for ext IRQ line + debug pads
2020-03-09 firmware-tof: release v0.2
2020-03-09 hardware: release v1 (sent to production)
2020-03-09 hardware: update libs (correct pin mapping in jst-gh, wrong in release v1)
2020-03-09 add example
